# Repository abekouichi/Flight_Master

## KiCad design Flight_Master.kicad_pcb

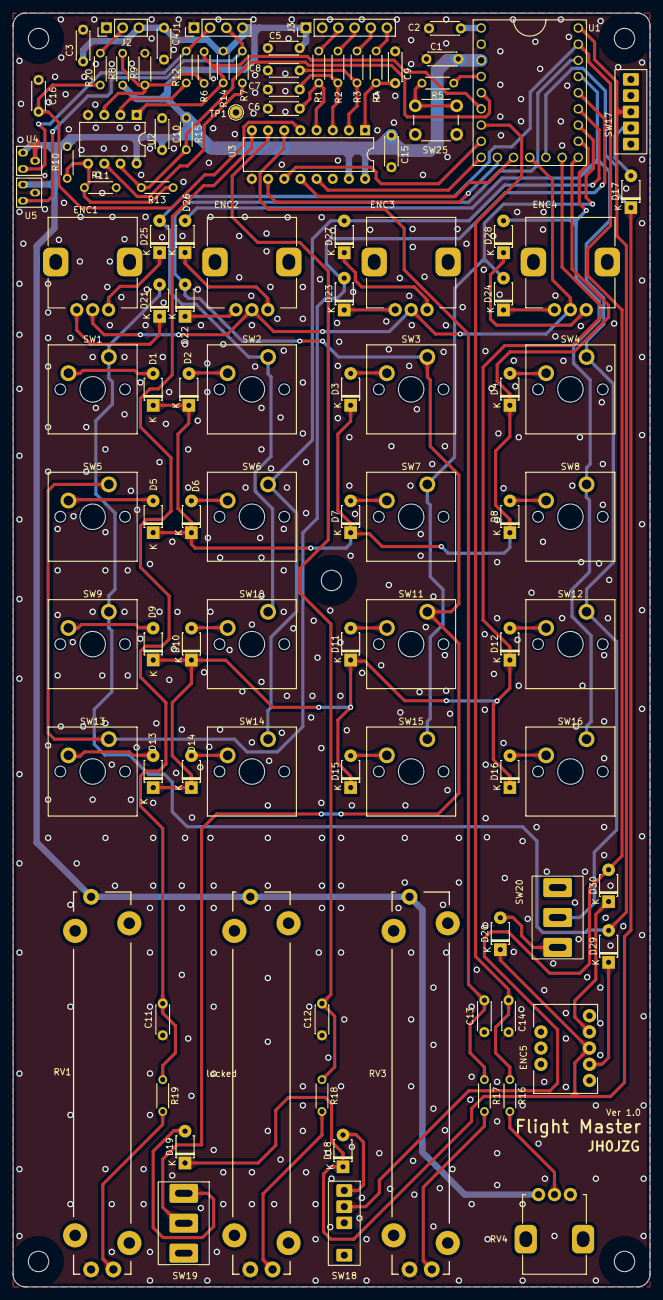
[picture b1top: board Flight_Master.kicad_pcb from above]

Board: 2 copper layers, 100.0 x 200.0 mm, 110 parts (0 on the bottom side), 77 nets.

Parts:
-: MountingHole_3.2mm_M3; MountingHole_3.2mm_M3_exclusion_beta
--: MountingHole_3.2mm_M3; MountingHole_3.2mm_M3_exclusion_beta
---: MountingHole_3.2mm_M3; MountingHole_3.2mm_M3_exclusion_beta
----: MountingHole_3.2mm_M3; MountingHole_3.2mm_M3_exclusion_beta
-----: MountingHole_3.2mm_M3; MountingHole_3.2mm_M3_exclusion_beta
C1, C2, C3, C4, C5, C6, C7, C8, C9, C10, C11, C12, C13, C14, C15, C16: C; C_Disc_D4.3mm_W1.9mm_P5.00mm_Hole0.8mm
D1, D2, D3, D4, D5, D6, D7, D8, D9, D10, D11, D12, D13, D14, D15, D16, D17, D18, D19, D20, D21, D22, D23, D24, D25, D26, D27, D28, D29, D30: D; D_T-1_P5.0mm_Horizontal_Hole0.8
ENC1, ENC2, ENC3, ENC4: EC12PL Rotary Encoder EC12E24
ENC5: Rotary Encoder Original Vertical
J1: Conn_01x04; PinHeader_1x04_P2.54mm_Vertical
J2: Conn_01x03; PinHeader_1x03_P2.54mm_Vertical
J3: Conn_01x06; PinHeader_1x06_P2.54mm_Vertical
R1, R2, R3, R4, R5, R6, R7, R8, R9, R10, R11, R12, R13, R14, R15, R16, R17, R18, R19, R20: R; R_Axial_DIN0204_L3.6mm_D1.6mm_P5.0mm_Hole0.8mm_Horizontal
RV1, RV3: R_Potentiometer_Trim_US; Slid_Volume_SL4515N
RV4: R_Potentiometer_Trim_US; ALPS Rotary Potentiometer RK09K11300DR
SW1, SW2, SW3, SW4, SW5, SW6, SW7, SW8, SW9, SW10, SW11, SW12, SW13, SW14, SW15, SW16: Cherry MX; SW_Cherry_MX_1.00u_PCB
SW17: SW_SPDT; Switch Toggle SPDT 3P-P2.54 Vertical with Fixpin
SW18: SW_SPDT; Switch Toggle SPDT 3P-P2.54 with Fixpin
SW19, SW20: SW_SPDT_NONLOCK; Switch Toggle SPDT 3P-P4.7
SW25: SW_Push; SW_PUSH_6mm
TP1: TestPoint; TestPoint_THTPad_D2.0mm_Drill1.0mm
U1: RP2040-ZERO
U2: LM393; DIP-8_W7.62mm
U3: MCP3008; DIP-16_W7.62mm
U4, U5: REF***; Hole_IC
locked: R_Potentiometer_Trim_US; Slid_Volume_SL4515N

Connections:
+3V3: C1.1, C3.1, C4.1, C5.1, C10.1, C15.1, J1.4, J2.3, J3.1, R8.1, R10.1, R14.1, R15.1, RV1.3, RV3.3, RV4.3, U1.3 (3V3), U2.8 (V+), U3.15 (Vref), U3.16 (Vdd), U4.1 (Vcc), U5.1 (Vcc), locked.3
+5V: C2.1, U1.1 (5V)
/ADC_AILRON: C16.1, R20.1, U3.5 (CH4)
/ADC_AIR_BRAKE: C11.1, R19.1, U3.8 (CH7)
/ADC_BRAKE_L: C7.1, R2.2, U3.3 (CH2)
/ADC_BRAKE_R: C6.1, R1.2, U3.4 (CH3)
/ADC_FLAP: C13.1, R17.1, U3.6 (CH5)
/ADC_RUDDER_L: C9.1, R4.2, U3.1 (CH0)
/ADC_RUDDER_R: C8.1, R3.2, U3.2 (CH1)
/ADC_THROTTLE: C12.1, R18.1, U3.7 (CH6)
/ADC_TILLER: C14.1, R16.1, U1.7 (GP26/ADC0/I2C1_SDA)
/COL0: D21.2 (A), D29.2 (A), SW1.1, SW9.1, SW17.2 (B), U1.23 (GP0/SPI0_RX/I2C0_SDA/UART0_TX)
/COL1: D25.2 (A), D30.2 (A), SW2.1, SW10.1, SW18.2 (B), U1.22 (GP1/SPI0_CSn/I2C0_SCL/UART0_RX)
/COL2: D22.2 (A), SW3.1, SW11.1, SW19.2 (B), U1.21 (GP2/SPI0_SCK/I2C1_SDA)
/COL3: D26.2 (A), SW4.1, SW12.1, SW20.2 (B), U1.20 (GP3/SPI0_TX/I2C1_SCL)
/COL4: D23.2 (A), SW5.1, SW13.1, U1.19 (GP4/SPI0_RX/I2C0_SDA/UART1_TX)
/COL5: D27.2 (A), SW6.1, SW14.1, U1.18 (GP5/SPI0_CSn/I2C0_SCL/UART1_RX)
/COL6: D24.2 (A), SW7.1, SW15.1, U1.17 (GP6/SPI0_SCK/I2C1_SDA)
/COL7: D28.2 (A), SW8.1, SW16.1, U1.16 (GP7/SPI0_TX/I2C1_SCL)
/ELEVATOR_0: R12.2, R14.2, U1.6 (GP27/ADC1/I2C1_SCL), U2.1
/ELEVATOR_1: R13.2, R15.2, U1.5 (GP28/ADC2), U2.7
/ELEVATOR_ZERO: R5.1, U1.4 (GP29/ADC3)
/ROW0: D1.1 (K), D2.1 (K), D3.1 (K), D4.1 (K), D5.1 (K), D6.1 (K), D7.1 (K), D8.1 (K), U1.15 (GP8/SPI1_RX/I2C0_SDA/UART1_TX)
/ROW1: D9.1 (K), D10.1 (K), D11.1 (K), D12.1 (K), D13.1 (K), D14.1 (K), D15.1 (K), D16.1 (K), U1.14 (GP9/SPI1_CSn/I2C0_SCL/UART1_RX)
/ROW2: D17.1 (K), D18.1 (K), D19.1 (K), D20.1 (K), ENC5.2 (C), U1.13 (GP10/SPI1_SCK/I2C1_SDA)
/ROW3: ENC1.2 (C), ENC2.2 (C), ENC3.2 (C), ENC4.2 (C), U1.12 (GP11/SPI1_TX/I2C1_SCL)
/SPI_CLK: U1.9 (GP14/SPI1_SCK/I2C1_SDA), U3.13 (CLK)
/SPI_CS: U1.10 (GP13/SPI1_CSn/I2C0_SCL/UART0_RX), U3.10 (~CS/SHDN)
/SPI_MISO: U1.11 (GP12/SPI1_RX/I2C0_SDA/UART0_TX), U3.12 (Dout)
/SPI_MOSI: U1.8 (GP15/SPI1_TX/I2C1_SCL), U3.11 (Din)
GND: C1.2, C2.2, C3.2, C4.2, C5.2, C6.2, C7.2, C8.2, C9.2, C10.2, C11.2, C12.2, C13.2, C14.2, C15.2, C16.2, J1.1, J2.1, J3.2, R9.2, R11.2, RV1.1, RV3.1, RV4.1, SW25.1, TP1.1, U1.2 (GND), U2.4 (V-), U3.9 (DGND), U3.14 (AGND), U4.2 (GND), U5.2 (GND), locked.1
unnamed: D1.2 (A), SW1.2
unnamed: D2.2 (A), SW2.2
unnamed: D3.2 (A), SW3.2
unnamed: D4.2 (A), SW4.2
unnamed: D5.2 (A), SW5.2
unnamed: D6.2 (A), SW6.2
unnamed: D7.2 (A), SW7.2
unnamed: D8.2 (A), SW8.2
unnamed: D9.2 (A), SW9.2
unnamed: D10.2 (A), SW10.2
unnamed: D11.2 (A), SW11.2
unnamed: D12.2 (A), SW12.2
unnamed: D13.2 (A), SW13.2
unnamed: D14.2 (A), SW14.2
unnamed: D15.2 (A), SW15.2
unnamed: D16.2 (A), SW16.2
unnamed: D17.2 (A), SW17.3 (C)
unnamed: D18.2 (A), SW18.3 (C)
unnamed: D19.2 (A), SW19.3 (C)
unnamed: D20.2 (A), SW20.3 (C)
unnamed: D21.1 (K), ENC1.1 (A)
unnamed: D22.1 (K), ENC2.1 (A)
unnamed: D23.1 (K), ENC3.1 (A)
unnamed: D24.1 (K), ENC4.1 (A)
unnamed: D25.1 (K), ENC1.3 (B)
unnamed: D26.1 (K), ENC2.3 (B)
unnamed: D27.1 (K), ENC3.3 (B)
unnamed: D28.1 (K), ENC4.3 (B)
unnamed: D29.1 (K), ENC5.1 (A)
unnamed: D30.1 (K), ENC5.3 (B)
unnamed: J1.2, R6.1, U4.3 (Out)
unnamed: J1.3, R7.1, U5.3 (Out)
unnamed: J2.2, R20.2
unnamed: J3.3, R1.1
unnamed: J3.4, R2.1
unnamed: J3.5, R3.1
unnamed: J3.6, R4.1
unnamed: R5.2, SW25.2
unnamed: R16.2, RV4.2
unnamed: R17.2, RV3.2
unnamed: R18.2, locked.2
unnamed: R19.2, RV1.2
unnamed: R8.2, R9.1, R12.1, U2.3 (+)
unnamed: R6.2, U2.2 (-)
unnamed: R10.2, R11.1, R13.1, U2.5 (+)
unnamed: R7.2, U2.6 (-)
